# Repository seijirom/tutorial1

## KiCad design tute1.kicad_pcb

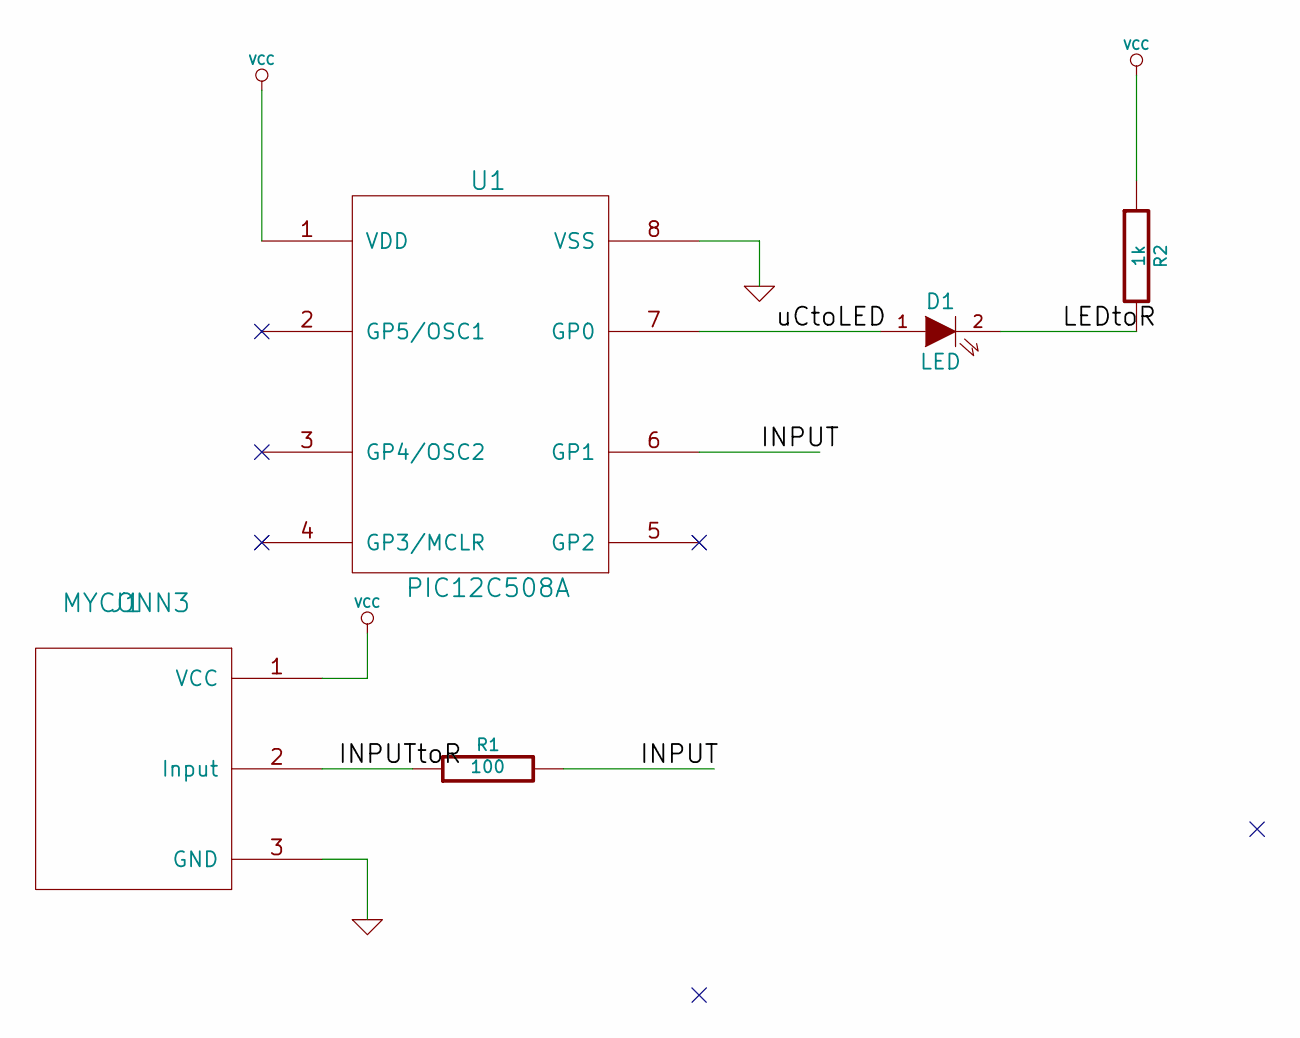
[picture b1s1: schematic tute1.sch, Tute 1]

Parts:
D1: LED
J1: MYCONN3
R1: 100
R2: 1k
U1: PIC12C508A

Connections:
/INPUT: R1.2, U1.6 (GP1)
/INPUTtoR: J1.2 (Input), R1.1
/LEDtoR: D1.2 (K), R2.2
/uCtoLED: D1.1 (A), U1.7 (GP0)
GND: J1.3 (GND), U1.8 (VSS)
VCC: J1.1 (VCC), R2.1, U1.1 (VDD)

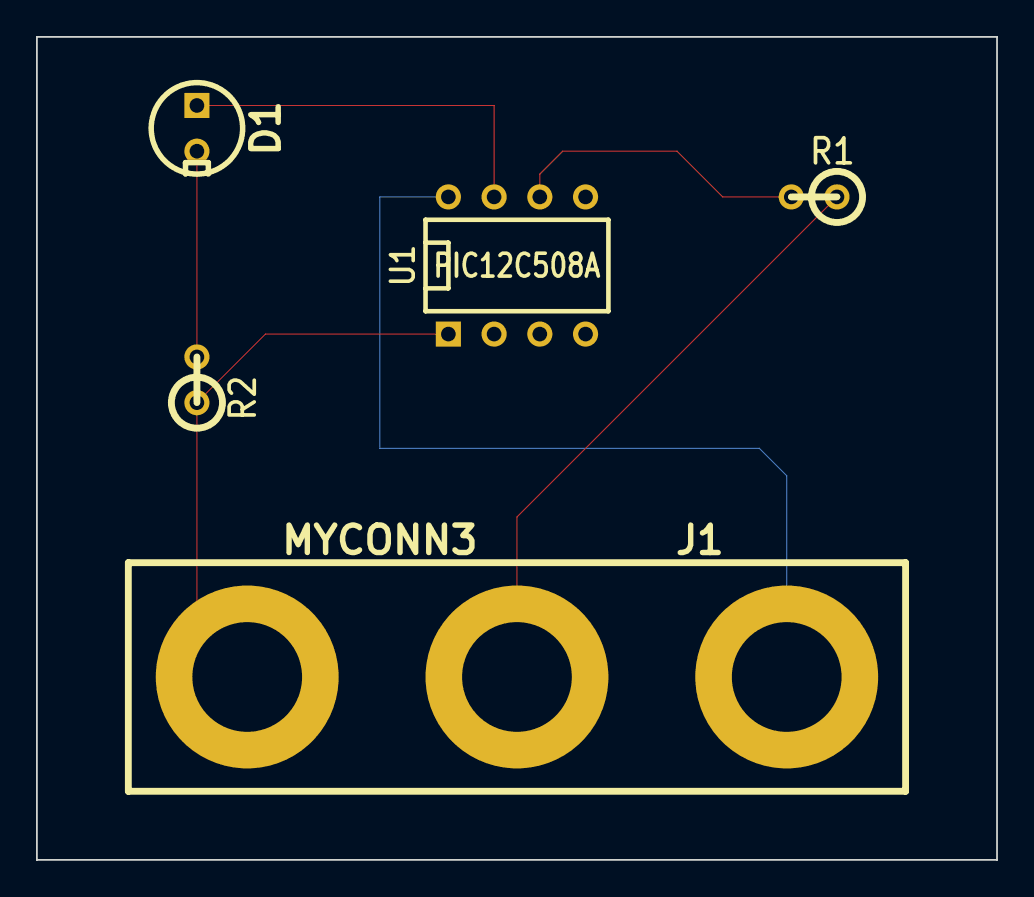
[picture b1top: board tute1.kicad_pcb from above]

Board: 2 copper layers, 53.3 x 45.7 mm, 5 parts (0 on the bottom side), 6 nets.

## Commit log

2016-01-23 Add /home/anagix/KiCad_samples/tute1
